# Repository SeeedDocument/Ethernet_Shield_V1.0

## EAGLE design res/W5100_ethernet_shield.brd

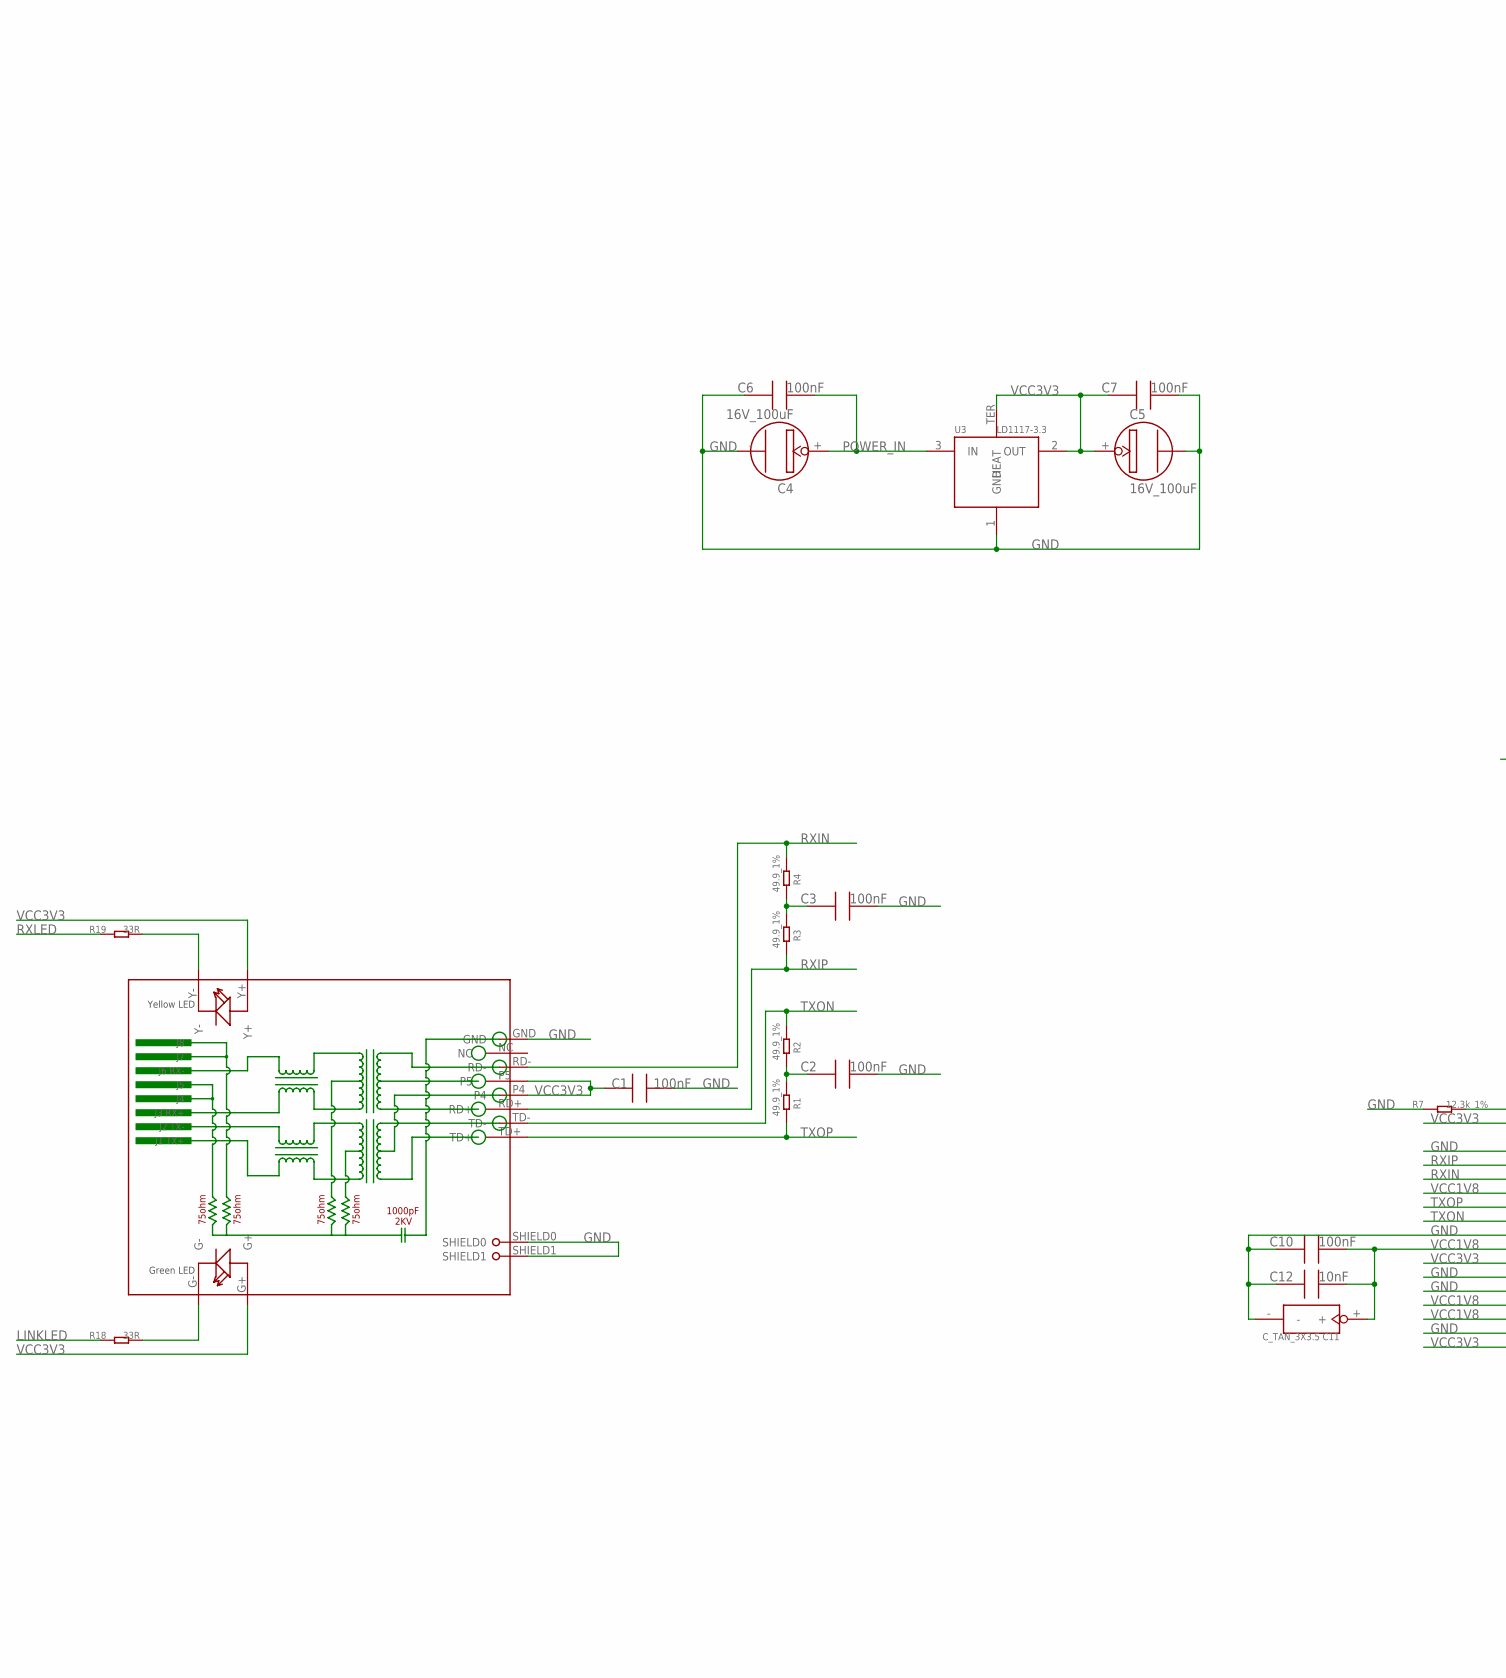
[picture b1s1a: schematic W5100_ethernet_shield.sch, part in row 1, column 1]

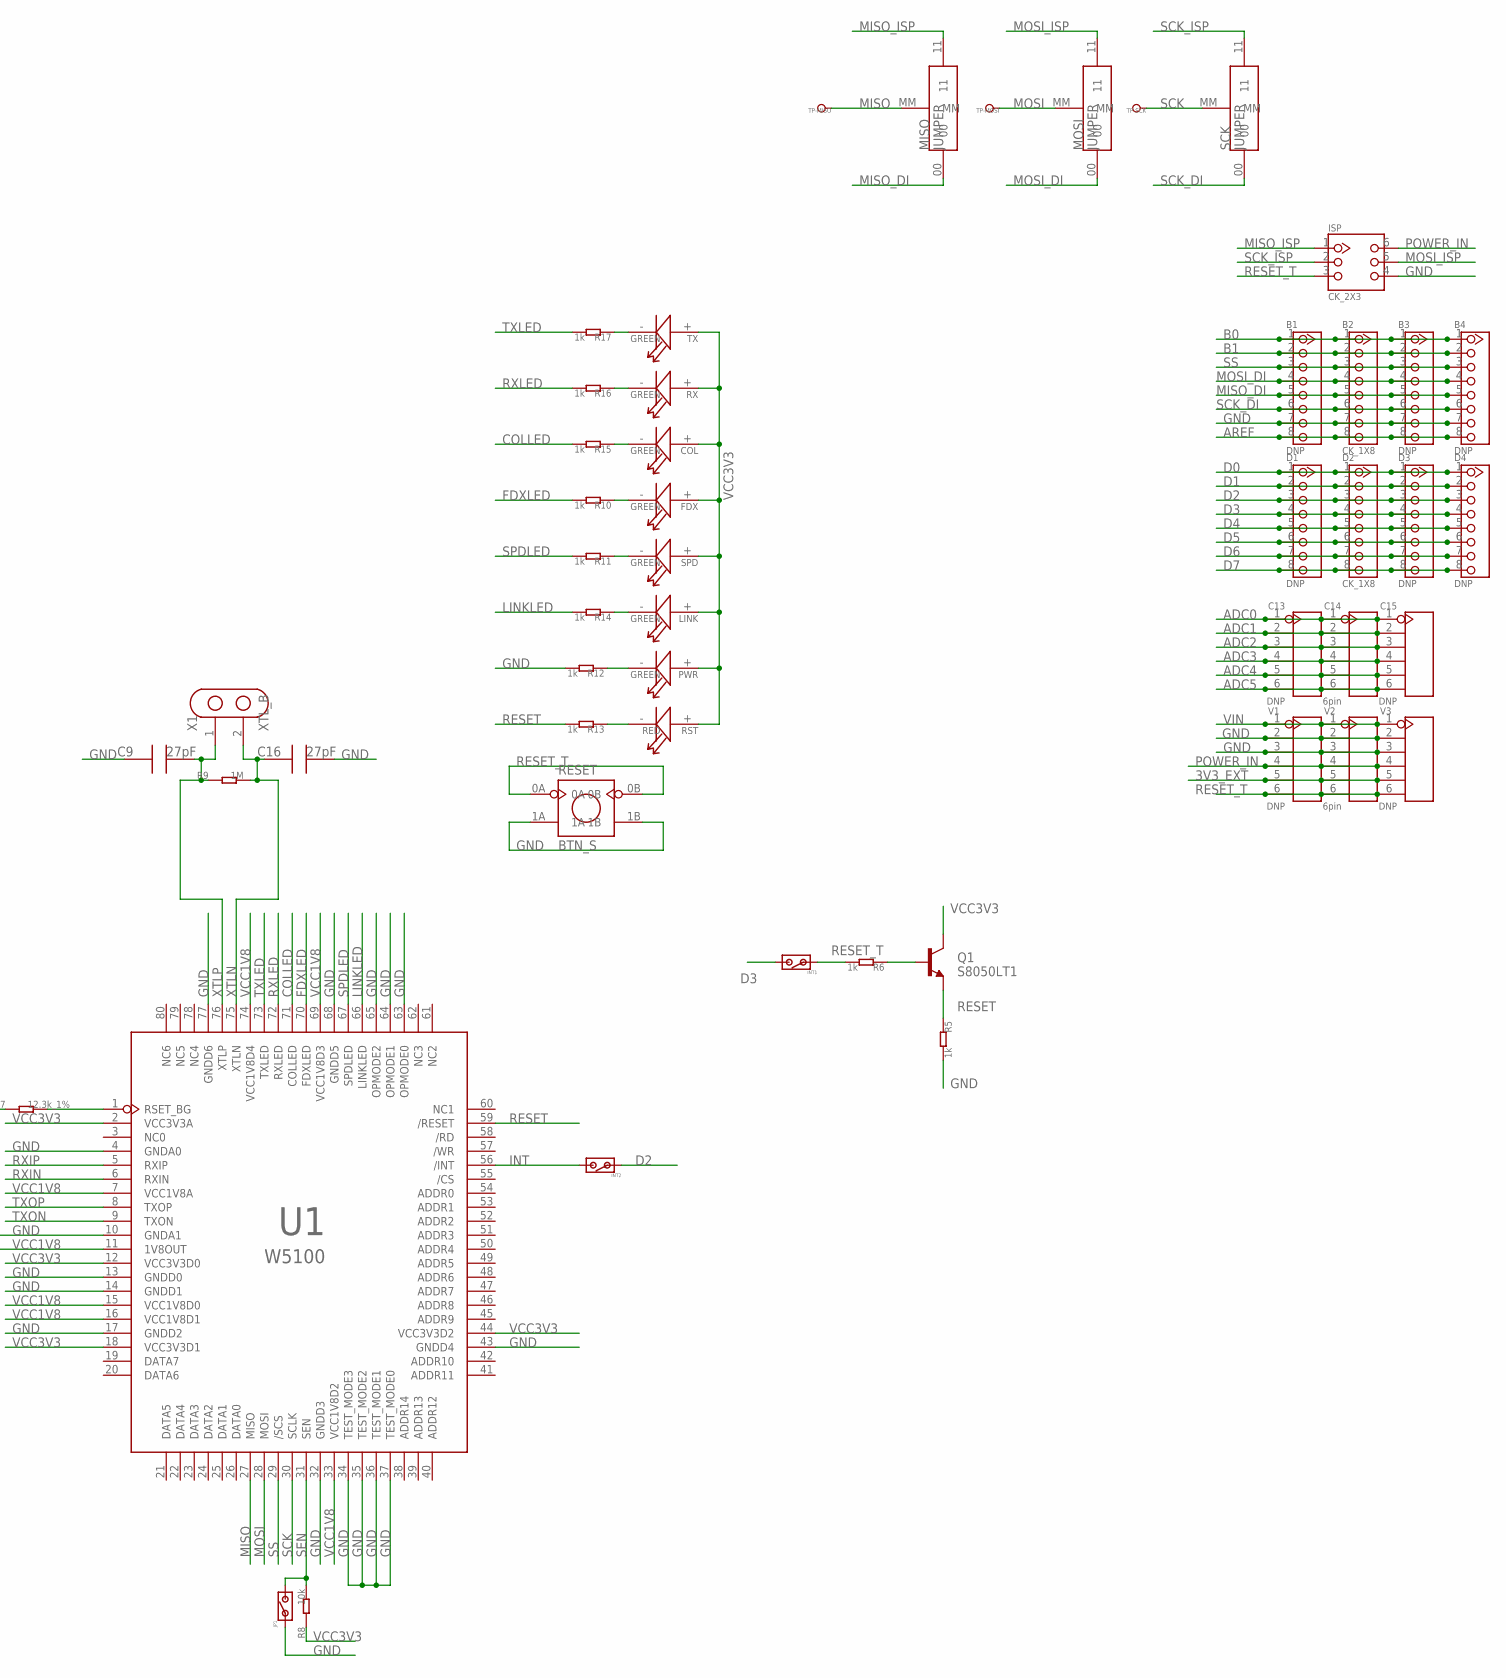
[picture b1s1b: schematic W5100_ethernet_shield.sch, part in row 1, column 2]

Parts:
B1, B3, B4: DNP; CK_1X8
B2: CK_1X8
C1, C2, C3, C6, C7, C10: 100nF; 0603
C4, C5: 16V_100uF; SANYO-OSCON_SMD_C6
C9, C16: 27pF; 0603
C11: C_TAN_3X3.5
C12: 10nF; 0603
C13, C15: DNP; CK_1*6
C14: 6pin; CK_1*6
COL: GREEN; LED0805
D1, D3, D4: DNP; CK_1X8
D2: CK_1X8
FDX: GREEN; LED0805
INT1, INT2: DNP; JP_SW
ISP: CK_2X3; CK_2X3_THIN
JP1: DNP; JP_SW
LINK: GREEN; LED0805
MISO: JUMPER
MOSI: JUMPER
PWR: GREEN; LED0805
Q1: S8050LT1; SOT23
R1, R2, R3, R4: 49.9_1%; 0603
R5, R6, R10, R11, R12, R13, R14, R15, R16, R17: 1k; 0603
R7: 12.3k_1%; 0603
R8: 10k; 0603
R9: 1M; 0603
R18, R19: 33R; 0603
RESET: BTN_S
RJ1: HR911105A
RST: RED; LED0805
RX: GREEN; LED0805
SCK: JUMPER
SPD: GREEN; LED0805
TP-MISO: DNP; TP_45X45
TP-MOSI: DNP; TP_45X45
TP-SCK: DNP; TP_45X45
TX: GREEN; LED0805
U1: W5100; SQFP80
U3: LD1117-3.3; SOT223
V1, V3: DNP; CK_1*6
V2: 6pin; CK_1*6
X1: XTL_B

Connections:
3V3_EXT: V1.5, V2.5, V3.5
ADC0: C13.1, C14.1, C15.1
ADC1: C13.2, C14.2, C15.2
ADC2: C13.3, C14.3, C15.3
ADC3: C13.4, C14.4, C15.4
ADC4: C13.5, C14.5, C15.5
ADC5: C13.6, C14.6, C15.6
AREF: B1.8, B2.8, B3.8, B4.8
B0: B1.1, B2.1, B3.1, B4.1
B1: B1.2, B2.2, B3.2, B4.2
COLLED: R15.2, U1.71 (COLLED)
D0: D1.1, D2.1, D3.1, D4.1
D1: D1.2, D2.2, D3.2, D4.2
D2: D1.3, D2.3, D3.3, D4.3, INT2.1
D3: D1.4, D2.4, D3.4, D4.4, INT1.2
D4: D1.5, D2.5, D3.5, D4.5
D5: D1.6, D2.6, D3.6, D4.6
D6: D1.7, D2.7, D3.7, D4.7
D7: D1.8, D2.8, D3.8, D4.8
FDXLED: R10.2, U1.70 (FDXLED)
GND: B1.7, B2.7, B3.7, B4.7, C1.2, C2.2, C3.2, C4.-, C5.-, C6.1, C7.2, C9.1, C10.1, C11.-, C12.1, C16.2, ISP.4, JP1.1, R5.2, R7.1, R12.2, RESET.1A, RESET.1B, RJ1.GND, RJ1.SHIELD0, RJ1.SHIELD1, U1.4 (GNDA0), U1.10 (GNDA1), U1.13 (GNDD0), U1.14 (GNDD1), U1.17 (GNDD2), U1.32 (GNDD3), U1.34 (TEST_MODE3), U1.35 (TEST_MODE2), U1.36 (TEST_MODE1), U1.37 (TEST_MODE0), U1.43 (GNDD4), U1.63 (OPMODE0), U1.64 (OPMODE1), U1.65 (OPMODE2), U1.68 (GNDD5), U1.77 (GNDD6), U3.1 (GND), V1.2, V1.3, V2.2, V2.3, V3.2, V3.3
INT: INT2.2, U1.56 (/INT)
LINKLED: R14.2, R18.1, U1.66 (LINKLED)
MISO: MISO.MM, TP-MISO.T, U1.27 (MISO)
MISO_DI: B1.5, B2.5, B3.5, B4.5, MISO.00
MISO_ISP: ISP.1, MISO.11
MOSI: MOSI.MM, TP-MOSI.T, U1.28 (MOSI)
MOSI_DI: B1.4, B2.4, B3.4, B4.4, MOSI.00
MOSI_ISP: ISP.5, MOSI.11
unnamed: C2.1, R1.1, R2.2
unnamed: R19.2, RJ1.Y-
unnamed: C3.1, R3.1, R4.2
unnamed: R18.2, RJ1.G-
unnamed: PWR.-, R12.1
unnamed: R13.1, RST.-
unnamed: FDX.-, R10.1
unnamed: Q1.1 (B), R6.1
unnamed: R11.1, SPD.-
unnamed: LINK.-, R14.1
unnamed: COL.-, R15.1
unnamed: R16.1, RX.-
unnamed: R7.2, U1.1 (RSET_BG)
unnamed: R17.1, TX.-
POWER_IN: C4.+, C6.2, ISP.6, U3.3 (IN), V1.4, V2.4, V3.4
RESET: Q1.2 (E), R5.1, R13.2, U1.59 (/RESET)
RESET_T: INT1.1, ISP.3, R6.2, RESET.0A, RESET.0B, V1.6, V2.6, V3.6
RXIN: R4.1, RJ1.RD-, U1.6 (RXIN)
RXIP: R3.2, RJ1.RD+, U1.5 (RXIP)
RXLED: R16.2, R19.1, U1.72 (RXLED)
SCK: SCK.MM, TP-SCK.T, U1.30 (SCLK)
SCK_DI: B1.6, B2.6, B3.6, B4.6, SCK.00
SCK_ISP: ISP.2, SCK.11
SEN: JP1.2, R8.2, U1.31 (SEN)
SPDLED: R11.2, U1.67 (SPDLED)
SS: B1.3, B2.3, B3.3, B4.3, U1.29 (/SCS)
TXLED: R17.2, U1.73 (TXLED)
TXON: R2.1, RJ1.TD-, U1.9 (TXON)
TXOP: R1.2, RJ1.TD+, U1.8 (TXOP)
VCC1V8: C10.2, C11.+, C12.2, U1.7 (VCC1V8A), U1.11 (1V8OUT), U1.15 (VCC1V8D0), U1.16 (VCC1V8D1), U1.33 (VCC1V8D2), U1.69 (VCC1V8D3), U1.74 (VCC1V8D4)
VCC3V3: C1.1, C5.+, C7.1, COL.+, FDX.+, LINK.+, PWR.+, Q1.3 (C), R8.1, RJ1.G+, RJ1.P4, RJ1.P5, RJ1.Y+, RST.+, RX.+, SPD.+, TX.+, U1.2 (VCC3V3A), U1.12 (VCC3V3D0), U1.18 (VCC3V3D1), U1.44 (VCC3V3D2), U3.2 (OUT), U3.TER (HEAT)
VIN: V1.1, V2.1, V3.1
XTLN: C16.1, R9.2, U1.75 (XTLN), X1.2
XTLP: C9.2, R9.1, U1.76 (XTLP), X1.1

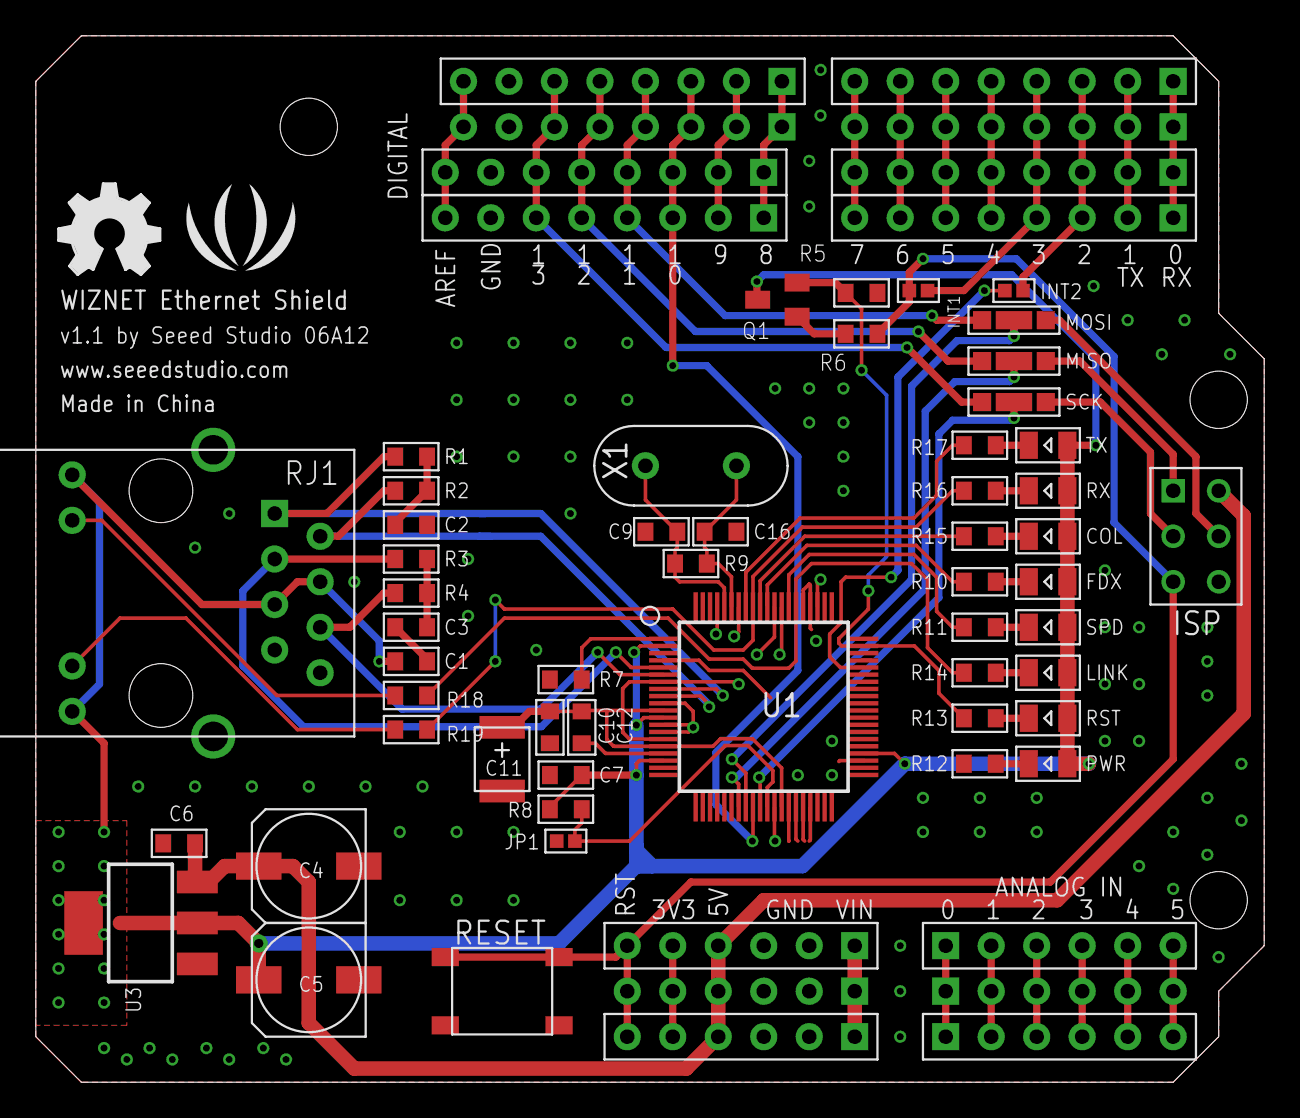
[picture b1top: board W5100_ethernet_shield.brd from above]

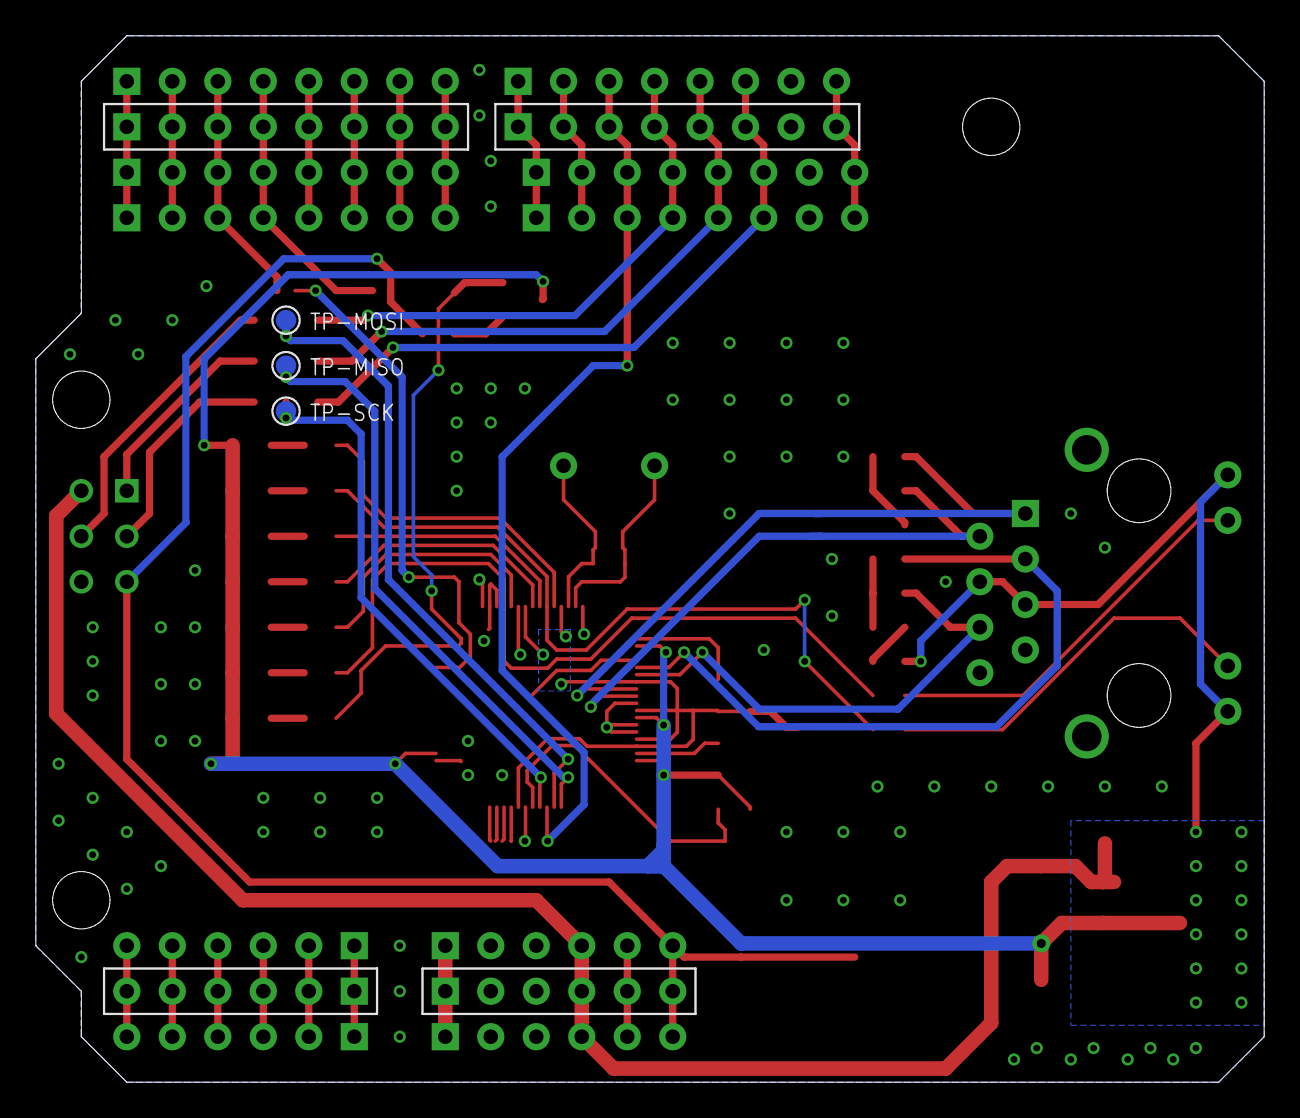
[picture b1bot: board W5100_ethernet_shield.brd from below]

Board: 2 copper layers, 68.6 x 58.4 mm, 71 parts (7 on the bottom side), 63 nets.

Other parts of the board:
U$1: OSHW_FILLX200_NOTEXT
U$2: LOGO_SILK

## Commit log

2017-05-27 upgrade
2019-11-05 add
    add
